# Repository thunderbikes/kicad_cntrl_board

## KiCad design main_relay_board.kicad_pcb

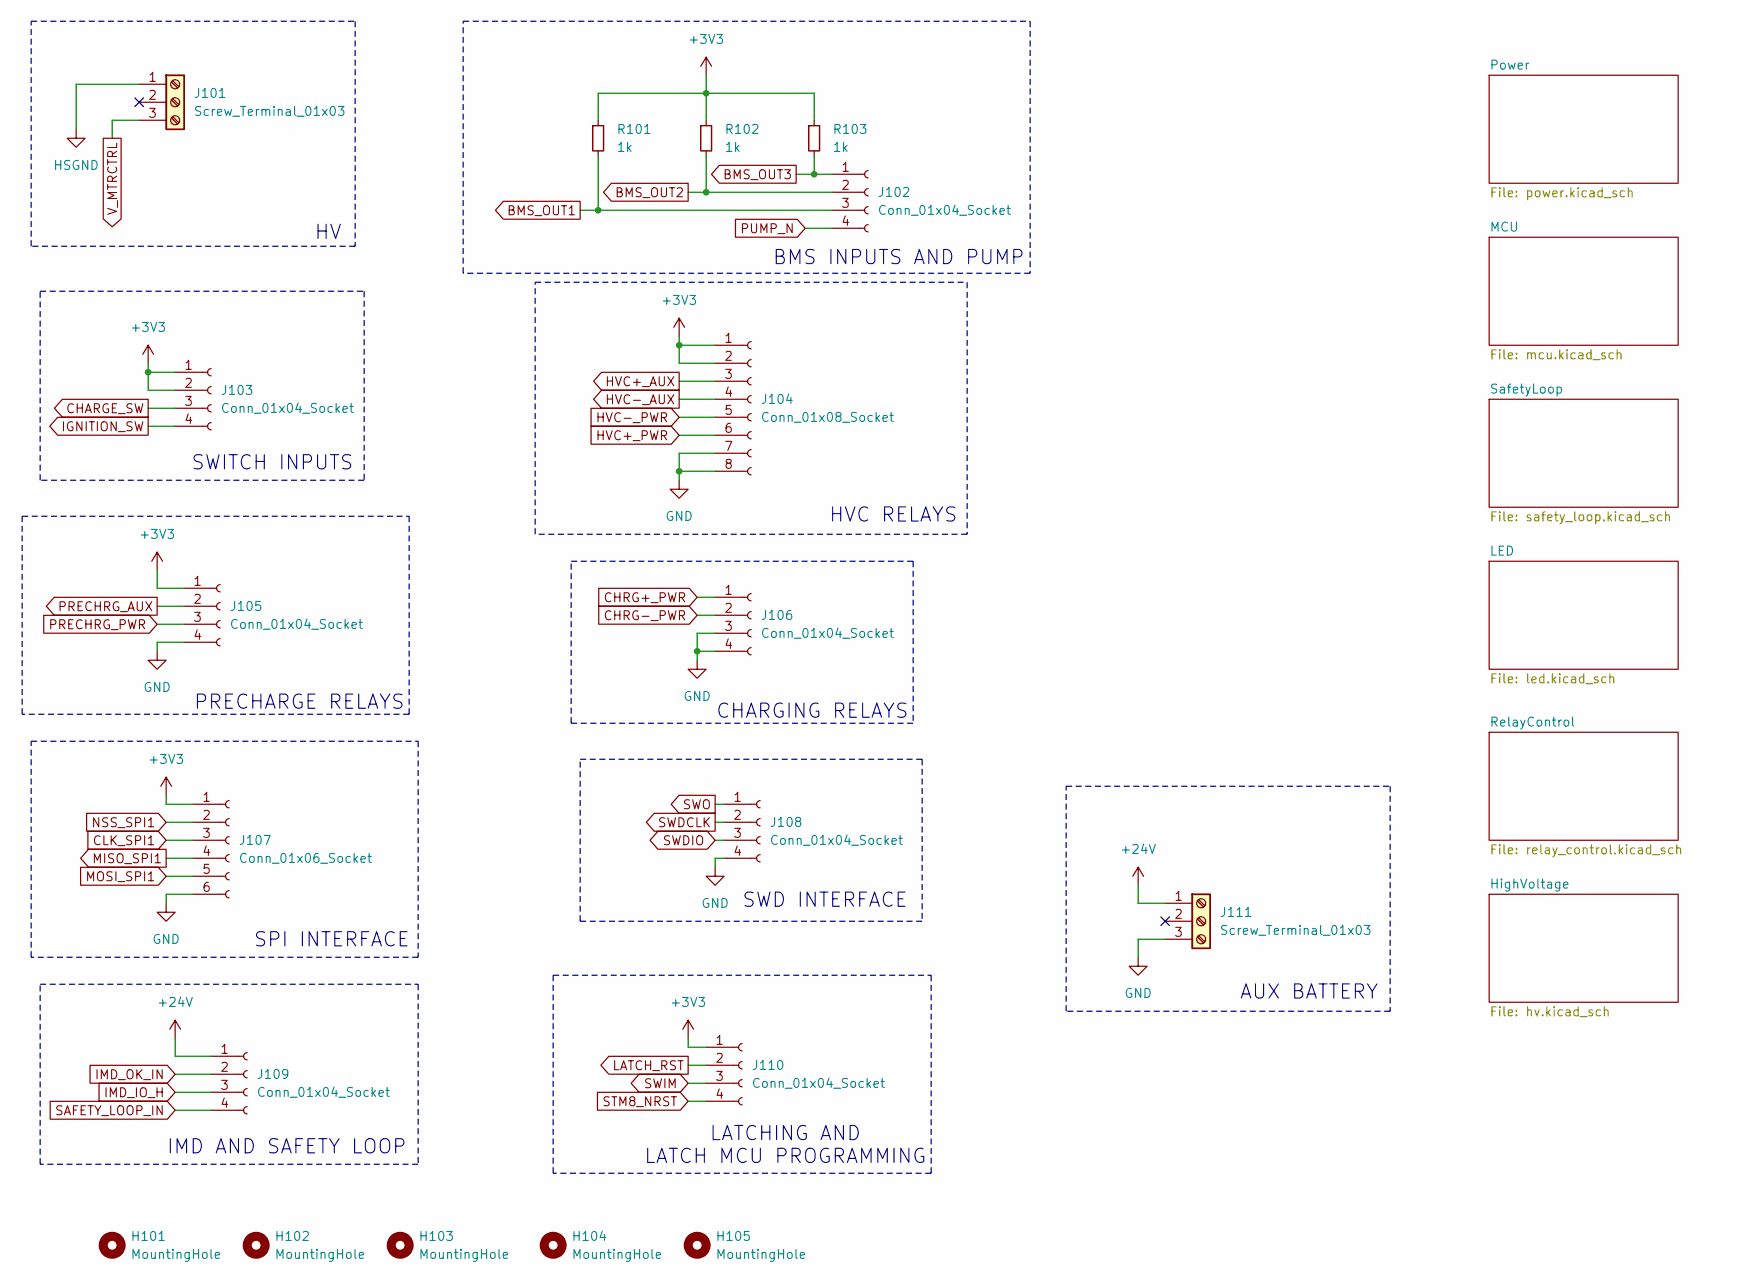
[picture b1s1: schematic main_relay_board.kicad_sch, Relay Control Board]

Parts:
H101, H102, H103, H104, H105: MountingHole; MountingHole_3mm
J101, J111: Screw_Terminal_01x03; TerminalBlock_Phoenix_MKDS-1,5-3-5.08_1x03_P5.08mm_Horizont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
J102, J103, J105, J106, J108, J109, J110: Conn_01x04_Socket; Molex_Mini-Fit_Jr_5566-04A_2x02_P4.20mm_Vertical
J104: Conn_01x08_Socket; Molex_Mini-Fit_Jr_5566-08A_2x04_P4.20mm_Vertical
J107: Conn_01x06_Socket; Molex_Mini-Fit_Jr_5566-06A_2x03_P4.20mm_Vertical
R101, R102, R103: 1k; R_0603_1608Metric; LCSC C22548

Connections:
+24V: J109.1, J111.1; also elsewhere on the board
BMS_OUT1: J102.3, R101.2; also elsewhere on the board
BMS_OUT2: J102.2, R102.2; also elsewhere on the board
BMS_OUT3: J102.1, R103.2; also elsewhere on the board
CHARGE_SW: J103.3; also elsewhere on the board
CHRG+_PWR: J106.1; also elsewhere on the board
CHRG-_PWR: J106.2; also elsewhere on the board
CLK_SPI1: J107.3; also elsewhere on the board
HVC+_AUX: J104.3; also elsewhere on the board
HVC+_PWR: J104.6; also elsewhere on the board
HVC-_AUX: J104.4; also elsewhere on the board
HVC-_PWR: J104.5; also elsewhere on the board
IGNITION_SW: J103.4; also elsewhere on the board
IMD_IO_H: J109.3; also elsewhere on the board
IMD_OK_IN: J109.2; also elsewhere on the board
LATCH_RST: J110.2; also elsewhere on the board
MISO_SPI1: J107.4; also elsewhere on the board
MOSI_SPI1: J107.5; also elsewhere on the board
NSS_SPI1: J107.2; also elsewhere on the board
PRECHRG_AUX: J105.2; also elsewhere on the board
PRECHRG_PWR: J105.3; also elsewhere on the board
PUMP_N: J102.4; also elsewhere on the board
SAFETY_LOOP_IN: J109.4; also elsewhere on the board
STM8_NRST: J110.4; also elsewhere on the board
SWDCLK: J108.2; also elsewhere on the board
SWDIO: J108.3; also elsewhere on the board
SWIM: J110.3; also elsewhere on the board
SWO: J108.1; also elsewhere on the board
V_MTRCTRL: J101.3; also elsewhere on the board

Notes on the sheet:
PRECHARGE RELAYS
BMS INPUTS AND PUMP
AUX BATTERY
CHARGING RELAYS
IMD AND SAFETY LOOP
SWD INTERFACE
SWITCH INPUTS
SPI INTERFACE
LATCHING AND LATCH MCU PROGRAMMING
HVC RELAYS

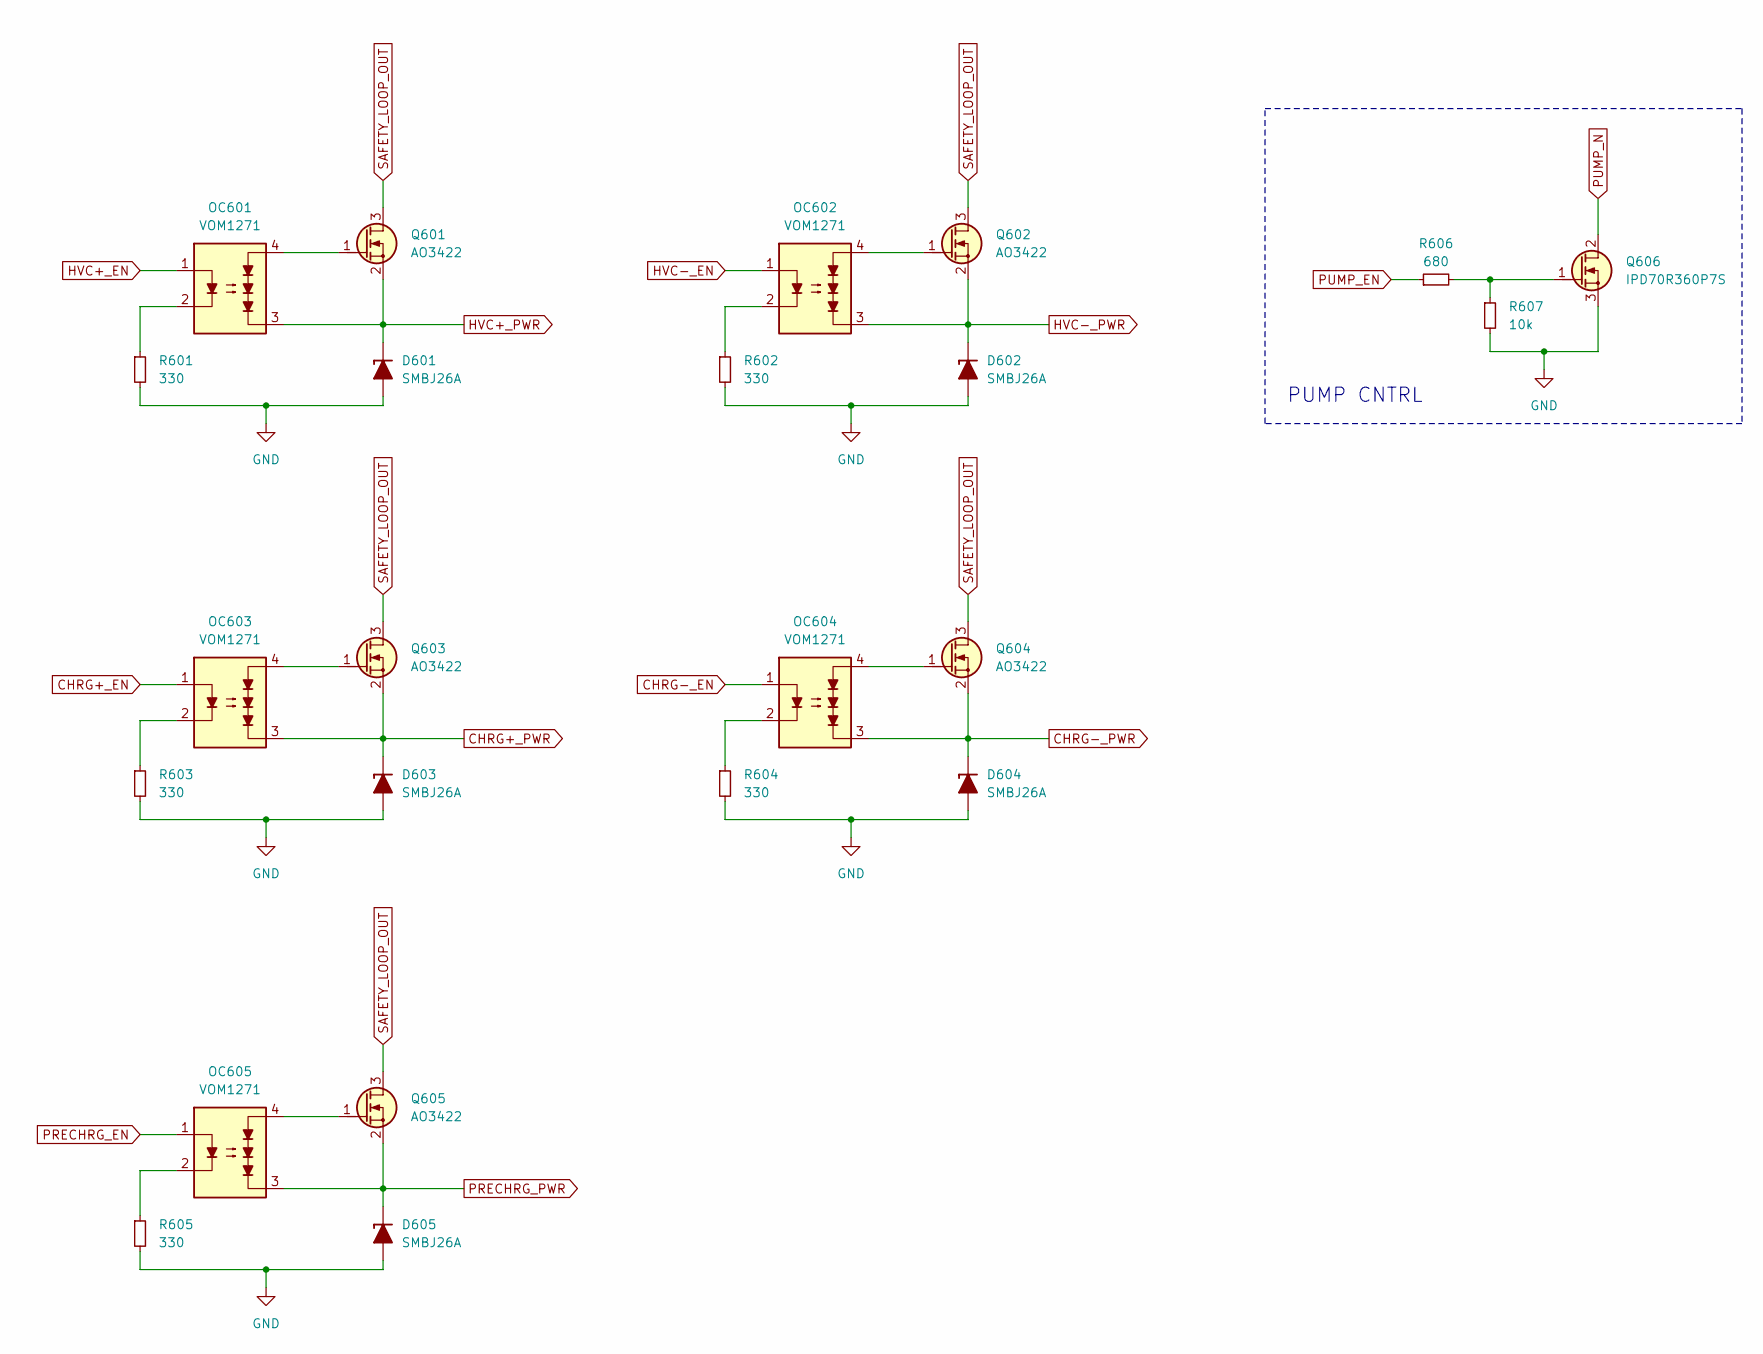
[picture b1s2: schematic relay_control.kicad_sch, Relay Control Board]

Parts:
D601, D602, D603, D604, D605: SMBJ26A; D_SMB; LCSC C2918418
OC601, OC602, OC603, OC604, OC605: VOM1271; SOIC254P695X242-4N; LCSC C146286
Q601, Q602, Q603, Q604, Q605: AO3422; SOT-23; LCSC C37130
Q606: IPD70R360P7S; TO-252-2; LCSC C151509
R601, R602, R603, R604, R605: 330; R_0603_1608Metric; LCSC C25804
R606: 680; R_0603_1608Metric; LCSC C23228
R607: 10k; R_0603_1608Metric; LCSC C25804

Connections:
CHRG+_EN: OC603.1; also elsewhere on the board
CHRG+_PWR: D603.1 (K), OC603.3, Q603.2 (S); also elsewhere on the board
CHRG-_EN: OC604.1; also elsewhere on the board
CHRG-_PWR: D604.1 (K), OC604.3, Q604.2 (S); also elsewhere on the board
HVC+_EN: OC601.1; also elsewhere on the board
HVC+_PWR: D601.1 (K), OC601.3, Q601.2 (S); also elsewhere on the board
HVC-_EN: OC602.1; also elsewhere on the board
HVC-_PWR: D602.1 (K), OC602.3, Q602.2 (S); also elsewhere on the board
unnamed: OC601.2, R601.1
unnamed: OC602.2, R602.1
unnamed: OC603.2, R603.1
unnamed: OC604.2, R604.1
unnamed: OC605.2, R605.1
unnamed: OC601.4, Q601.1 (G)
unnamed: OC602.4, Q602.1 (G)
unnamed: OC603.4, Q603.1 (G)
unnamed: OC604.4, Q604.1 (G)
unnamed: OC605.4, Q605.1 (G)
unnamed: Q606.1 (G), R606.2, R607.1
PRECHRG_EN: OC605.1; also elsewhere on the board
PRECHRG_PWR: D605.1 (K), OC605.3, Q605.2 (S); also elsewhere on the board
PUMP_EN: R606.1; also elsewhere on the board
PUMP_N: Q606.2 (D); also elsewhere on the board
SAFETY_LOOP_OUT: Q601.3 (D), Q602.3 (D), Q603.3 (D), Q604.3 (D), Q605.3 (D); also elsewhere on the board

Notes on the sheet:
PUMP CNTRL

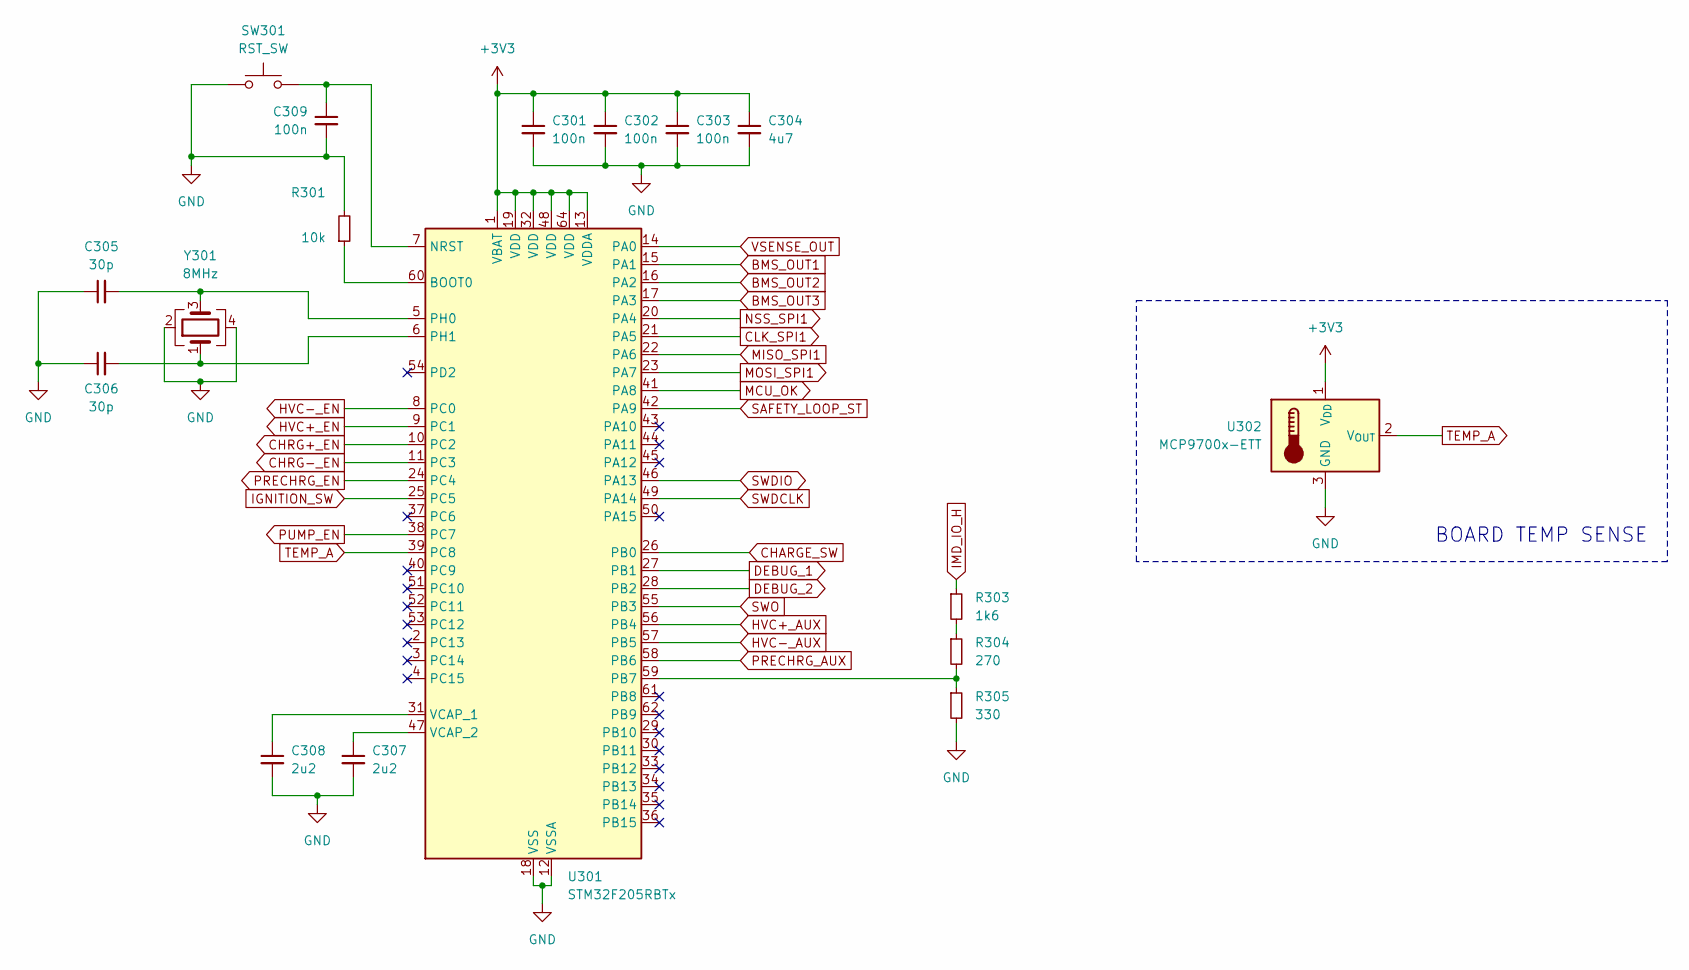
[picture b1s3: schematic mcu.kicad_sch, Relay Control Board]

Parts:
C301, C302, C303, C309: 100n; C_0603_1608Metric; LCSC C1591
C304: 4u7; C_0603_1608Metric; LCSC C108342
C305, C306: 30p; C_0603_1608Metric; LCSC C1853723
C307, C308: 2u2; C_0603_1608Metric; LCSC C99228
R301: 10k; R_0603_1608Metric; LCSC C25804
R303: 1k6; R_0603_1608Metric; LCSC C22847
R304: 270; R_0603_1608Metric; LCSC C22966
R305: 330; R_0603_1608Metric; LCSC C105881
SW301: RST_SW; SW_Tactile_SPST_NO_Straight_CK_PTS636Sx25SMTRLFS; LCSC C318938
U301: STM32F205RBTx; LQFP-64_10x10mm_P0.5mm; LCSC C8364
U302: MCP9700x-ETT; SOT-23; LCSC C127949
Y301: 8MHz; Crystal_SMD_3225-4Pin_3.2x2.5mm; LCSC C2682775

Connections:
BMS_OUT1: U301.15 (PA1); also elsewhere on the board
BMS_OUT2: U301.16 (PA2); also elsewhere on the board
BMS_OUT3: U301.17 (PA3); also elsewhere on the board
CHARGE_SW: U301.26 (PB0); also elsewhere on the board
CHRG+_EN: U301.10 (PC2); also elsewhere on the board
CHRG-_EN: U301.11 (PC3); also elsewhere on the board
CLK_SPI1: U301.21 (PA5); also elsewhere on the board
DEBUG_1: U301.27 (PB1); also elsewhere on the board
DEBUG_2: U301.28 (PB2); also elsewhere on the board
HVC+_AUX: U301.56 (PB4); also elsewhere on the board
HVC+_EN: U301.9 (PC1); also elsewhere on the board
HVC-_AUX: U301.57 (PB5); also elsewhere on the board
HVC-_EN: U301.8 (PC0); also elsewhere on the board
IGNITION_SW: U301.25 (PC5); also elsewhere on the board
IMD_IO_H: R303.1; also elsewhere on the board
MCU_OK: U301.41 (PA8); also elsewhere on the board
MISO_SPI1: U301.22 (PA6); also elsewhere on the board
MOSI_SPI1: U301.23 (PA7); also elsewhere on the board
NSS_SPI1: U301.20 (PA4); also elsewhere on the board
unnamed: R303.2, R304.1
unnamed: R301.1, U301.60 (BOOT0)
unnamed: C309.1, SW301.2, U301.7 (NRST)
unnamed: R304.2, R305.1, U301.59 (PB7)
unnamed: C305.2, U301.5 (PH0), Y301.3
unnamed: C306.2, U301.6 (PH1), Y301.1
unnamed: C308.1, U301.31 (VCAP_1)
unnamed: C307.1, U301.47 (VCAP_2)
PRECHRG_AUX: U301.58 (PB6); also elsewhere on the board
PRECHRG_EN: U301.24 (PC4); also elsewhere on the board
PUMP_EN: U301.38 (PC7); also elsewhere on the board
SAFETY_LOOP_ST: U301.42 (PA9); also elsewhere on the board
SWDCLK: U301.49 (PA14); also elsewhere on the board
SWDIO: U301.46 (PA13); also elsewhere on the board
SWO: U301.55 (PB3); also elsewhere on the board
TEMP_A: U301.39 (PC8), U302.2 (V_{OUT})
VSENSE_OUT: U301.14 (PA0); also elsewhere on the board

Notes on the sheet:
BOARD TEMP SENSE

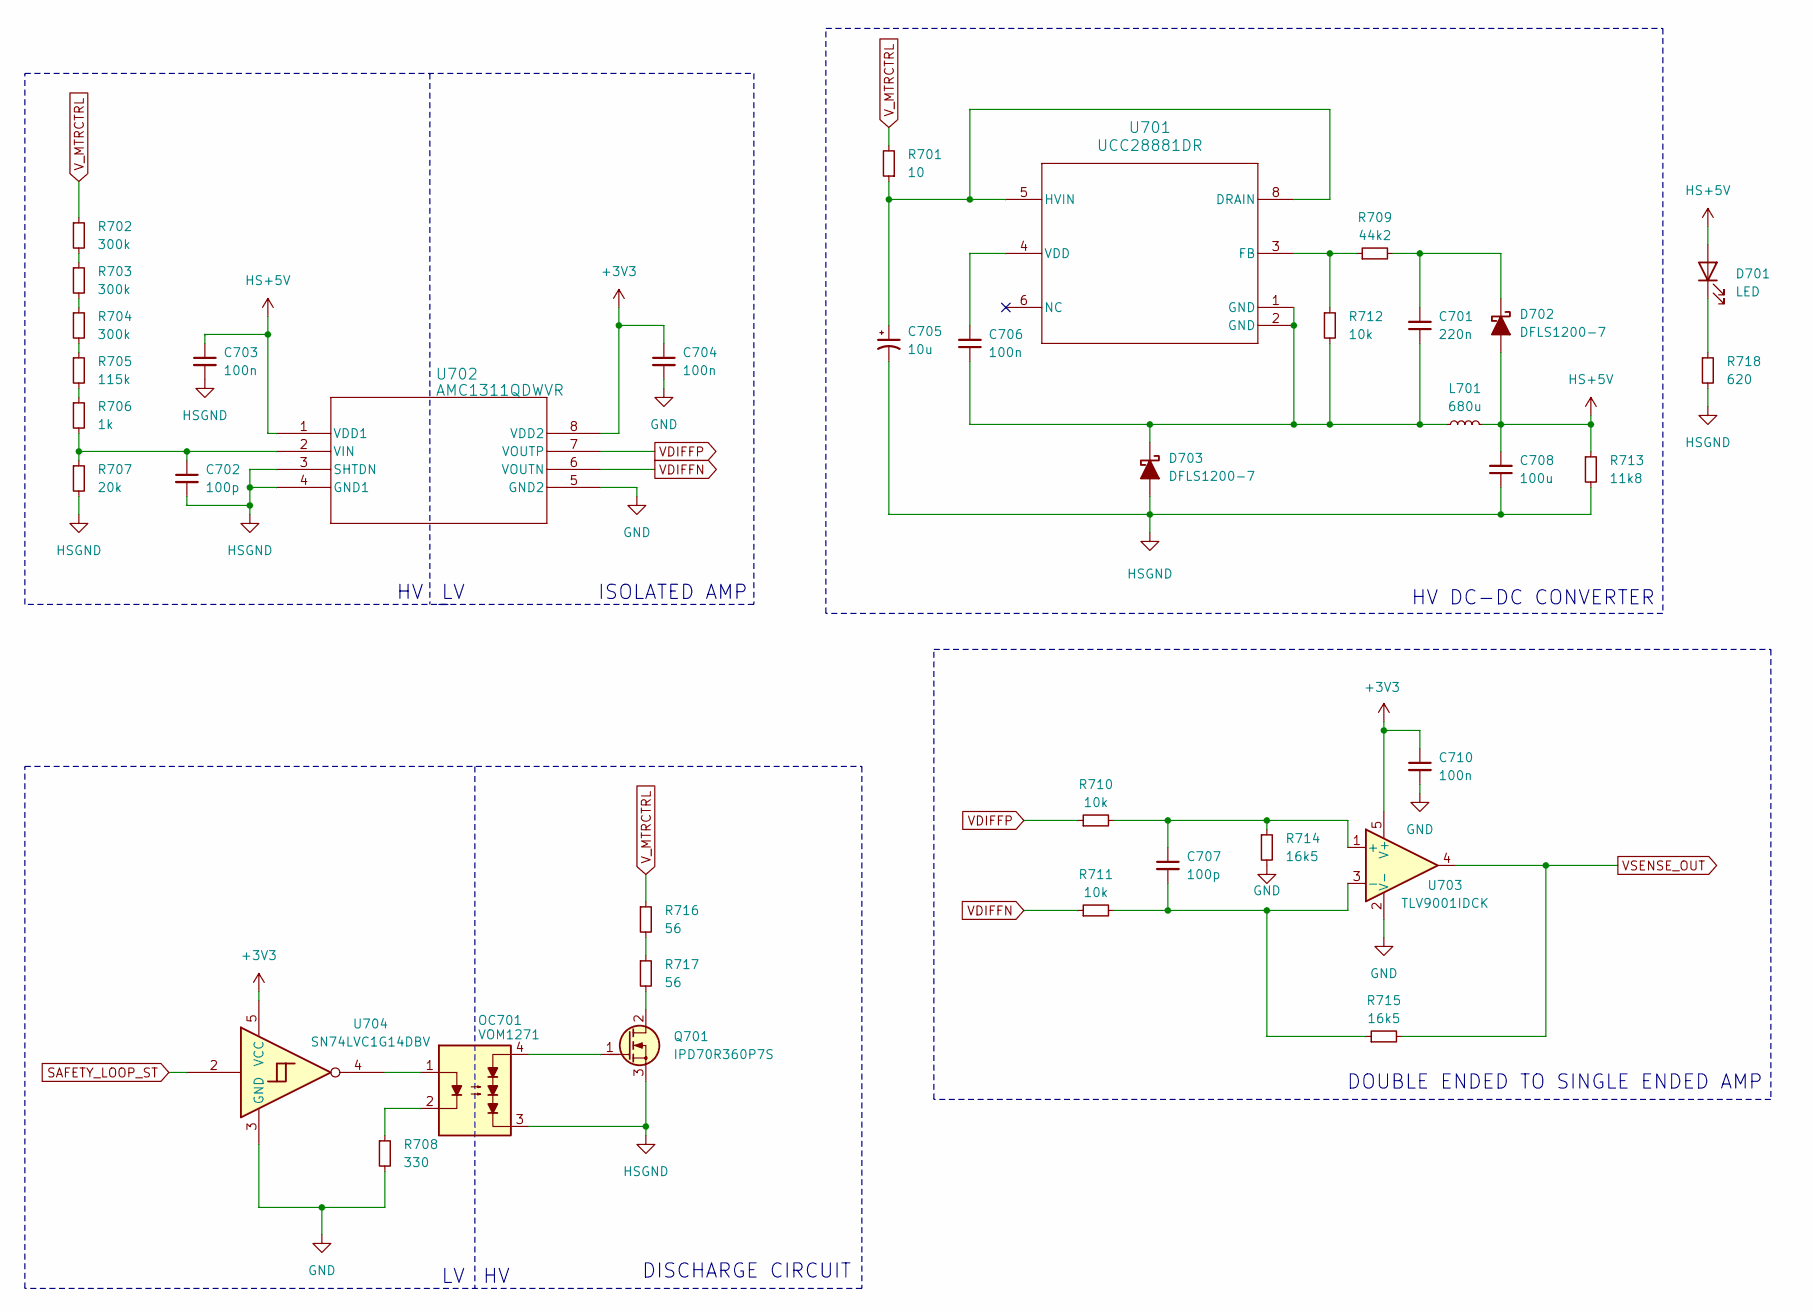
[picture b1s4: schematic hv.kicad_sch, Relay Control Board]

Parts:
C701: 220n; C_0603_1608Metric; LCSC C21120
C702, C707: 100p; C_0603_1608Metric; LCSC C160903
C703, C704, C706, C710: 100n; C_0603_1608Metric; LCSC C1591
C705: 10u; CP_Radial_D10.0mm_P5.00mm; DigiKey P13540-ND
C708: 100u; C_1206_3216Metric; LCSC C15008
D701: LED; LED_0603_1608Metric; LCSC C84263
D702, D703: DFLS1200-7; D_PowerDI-123; LCSC C324985
L701: 680u; L_12x12mm_H8mm; LCSC C2455611
OC701: VOM1271; SOIC254P695X242-4N; LCSC C146286
Q701: IPD70R360P7S; TO-252-2; LCSC C151509
R701: 10; R_0603_1608Metric; LCSC C22859
R702, R703, R704: 300k; R_0603_1608Metric; LCSC C23024
R705: 115k; R_0603_1608Metric; LCSC C3016434
R706: 1k; R_0603_1608Metric; LCSC C22548
R707: 20k; R_0603_1608Metric; LCSC C4184
R708: 330; R_0603_1608Metric; LCSC C105881
R709: 44k2; R_0603_1608Metric; LCSC C23056
R710, R711, R712: 10k; R_0603_1608Metric; LCSC C25804
R713: 11k8; R_0402_1005Metric; LCSC C481934
R714, R715: 16k5; R_0603_1608Metric; LCSC C2933155
R716, R717: 56; TO-247-2_Vertical; DigiKey 273-AP10156RF-ND
R718: 620; R_0603_1608Metric; LCSC C23220
U701: UCC28881DR; D0007A_N; LCSC C544970
U702: AMC1311QDWVR; DWV8_TEX; LCSC C456277
U703: TLV9001IDCK; SOT-353_SC-70-5; LCSC C398362
U704: SN74LVC1G14DBV; SOT-23-5; LCSC C434069

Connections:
HS+5V: C703.1, C708.2, D701.2 (A), D702.2 (A), L701.2, R713.1, U701.6 (+Vout), U702.1 (VDD1)
unnamed: D701.1 (K), R718.1
unnamed: OC701.1, U704.4
unnamed: OC701.2, R708.1
unnamed: Q701.2 (D), R717.2
unnamed: OC701.4, Q701.1 (G)
unnamed: R702.2, R703.1
unnamed: R703.2, R704.1
unnamed: R704.2, R705.1
unnamed: R705.2, R706.1
unnamed: R709.1, R712.1, U701.3 (FB)
unnamed: R716.2, R717.1
SAFETY_LOOP_ST: U704.2; also elsewhere on the board
VDIFFN: R711.1, U702.6 (VOUTN)
VDIFFP: R710.1, U702.7 (VOUTP)
VSENSE_OUT: R715.2, U703.4; also elsewhere on the board
V_MTRCTRL: R701.2, R702.1, R716.1; also elsewhere on the board

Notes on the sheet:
DISCHARGE CIRCUIT
ISOLATED AMP
DOUBLE ENDED TO SINGLE ENDED AMP
HV DC-DC CONVERTER

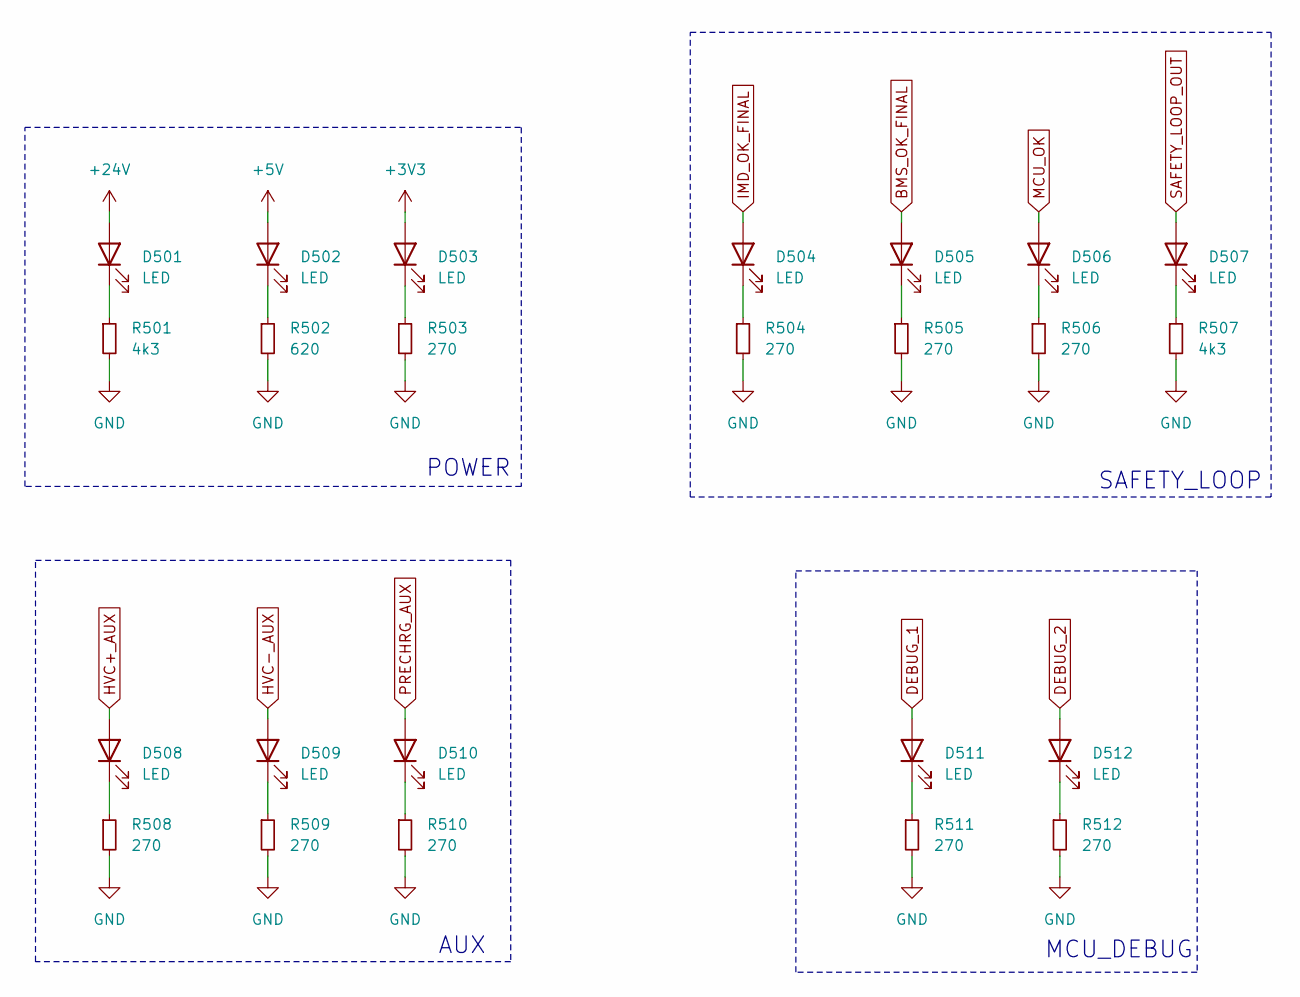
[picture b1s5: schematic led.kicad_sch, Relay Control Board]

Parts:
D501, D502, D503, D504, D505, D506, D507, D508, D509, D510, D511, D512: LED; LED_0603_1608Metric; LCSC C84263
R501, R507: 4k3; R_0603_1608Metric; LCSC C23159
R502: 620; R_0603_1608Metric; LCSC C23220
R503, R504, R505, R506, R508, R509, R510, R511, R512: 270; R_0603_1608Metric; LCSC C22966

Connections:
+24V: D501.2 (A); also elsewhere on the board
BMS_OK_FINAL: D505.2 (A); also elsewhere on the board
DEBUG_1: D511.2 (A); also elsewhere on the board
DEBUG_2: D512.2 (A); also elsewhere on the board
HVC+_AUX: D508.2 (A); also elsewhere on the board
HVC-_AUX: D509.2 (A); also elsewhere on the board
IMD_OK_FINAL: D504.2 (A); also elsewhere on the board
MCU_OK: D506.2 (A); also elsewhere on the board
unnamed: D501.1 (K), R501.1
unnamed: D502.1 (K), R502.1
unnamed: D503.1 (K), R503.1
unnamed: D504.1 (K), R504.1
unnamed: D505.1 (K), R505.1
unnamed: D506.1 (K), R506.1
unnamed: D507.1 (K), R507.1
unnamed: D508.1 (K), R508.1
unnamed: D509.1 (K), R509.1
unnamed: D510.1 (K), R510.1
unnamed: D511.1 (K), R511.1
unnamed: D512.1 (K), R512.1
PRECHRG_AUX: D510.2 (A); also elsewhere on the board
SAFETY_LOOP_OUT: D507.2 (A); also elsewhere on the board

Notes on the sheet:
SAFETY_LOOP
MCU_DEBUG
POWER
AUX

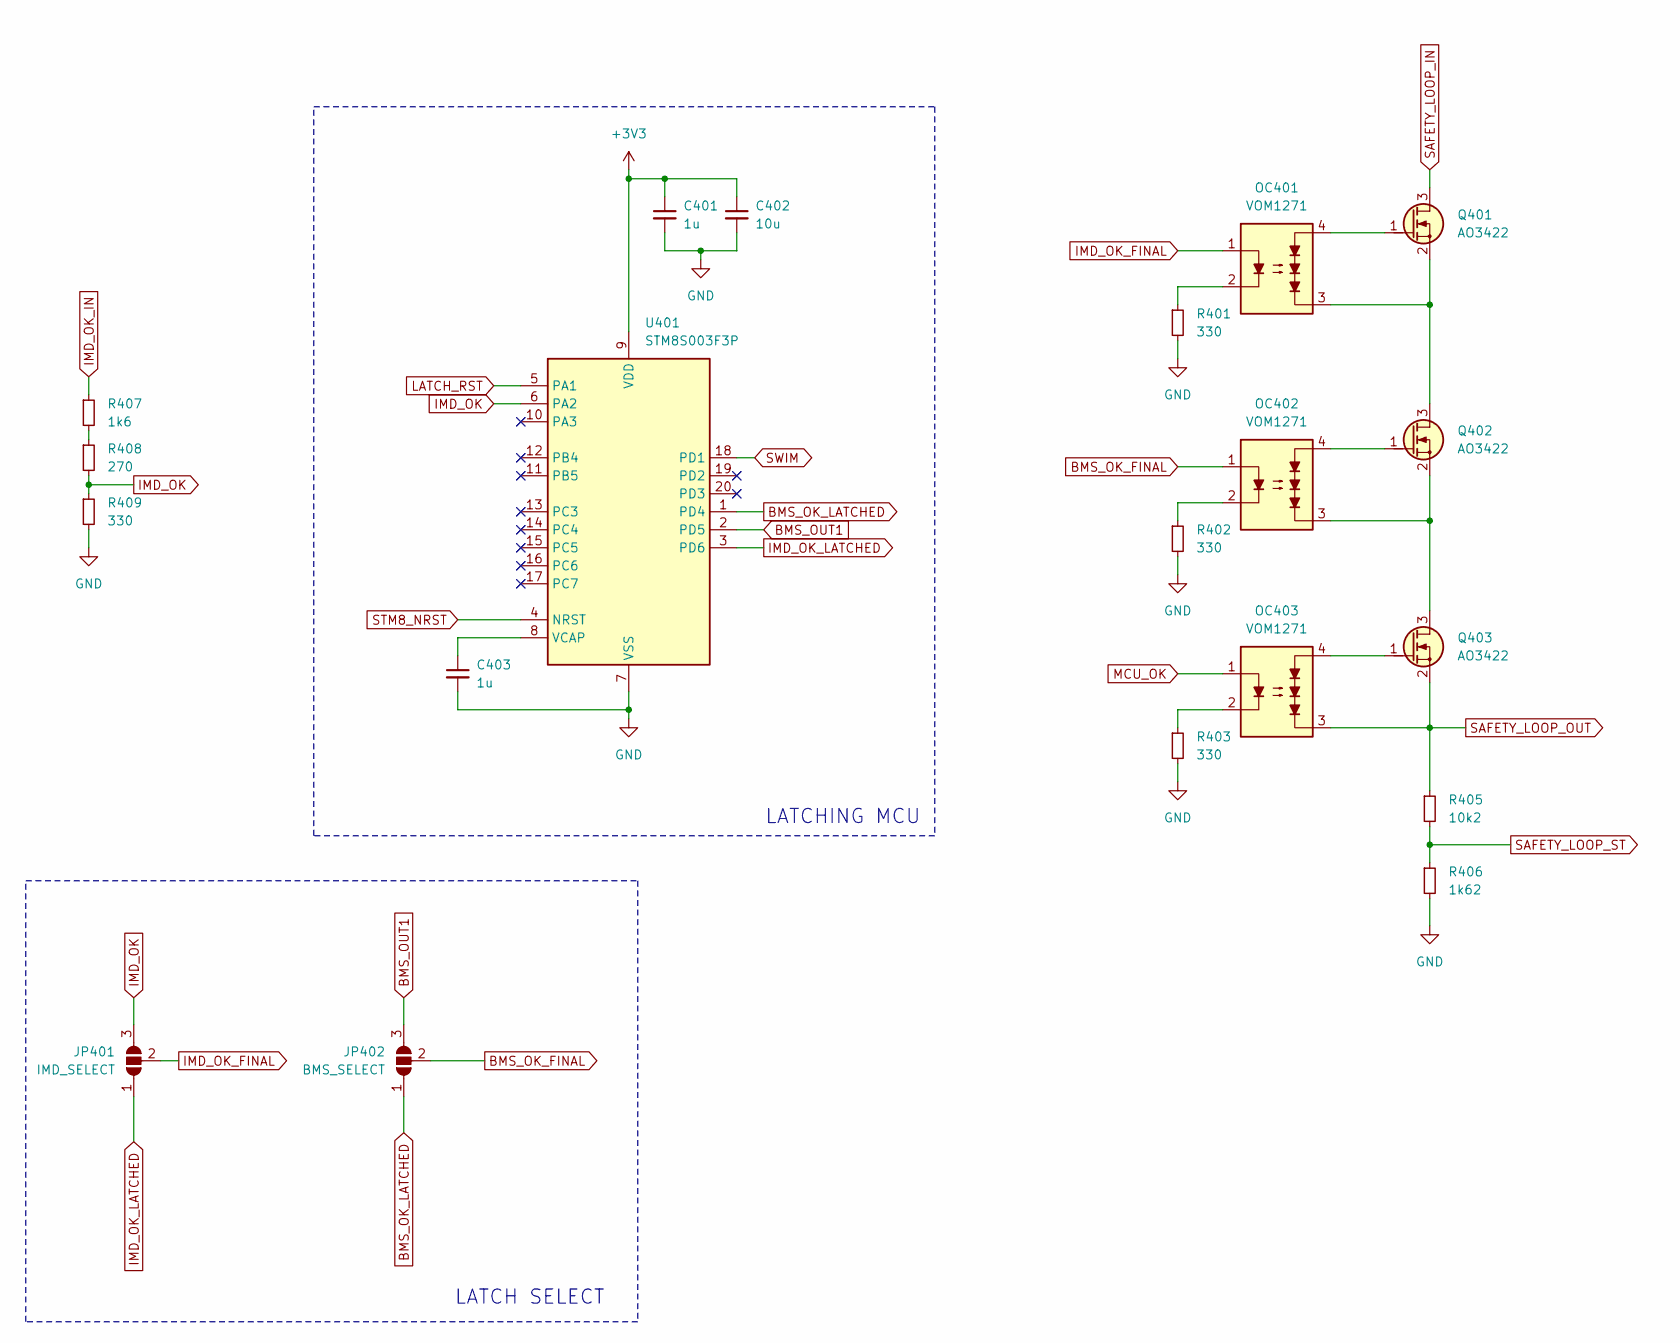
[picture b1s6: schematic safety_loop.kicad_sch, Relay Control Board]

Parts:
C401, C403: 1u; C_0603_1608Metric; LCSC C59302
C402: 10u; C_0603_1608Metric; LCSC C91606
JP401: IMD_SELECT; SolderJumper-3_P1.3mm_Open_Pad1.0x1.5mm
JP402: BMS_SELECT; SolderJumper-3_P1.3mm_Open_Pad1.0x1.5mm
OC401, OC402, OC403: VOM1271; SOIC254P695X242-4N; LCSC C146286
Q401, Q402, Q403: AO3422; SOT-23; LCSC C37130
R401, R402, R403, R409: 330; R_0603_1608Metric; LCSC C105881
R405: 10k2; R_0603_1608Metric; LCSC C22772
R406: 1k62; R_0603_1608Metric; LCSC C22844
R407: 1k6; R_0603_1608Metric; LCSC C22847
R408: 270; R_0603_1608Metric; LCSC C22966
U401: STM8S003F3P; TSSOP-20_4.4x6.5mm_P0.65mm; LCSC C52717

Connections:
BMS_OK_FINAL: JP402.2 (C), OC402.1; also elsewhere on the board
BMS_OK_LATCHED: JP402.1 (A), U401.1 (PD4)
BMS_OUT1: JP402.3 (B), U401.2 (PD5); also elsewhere on the board
IMD_OK: JP401.3 (B), R408.2, R409.1, U401.6 (PA2)
IMD_OK_FINAL: JP401.2 (C), OC401.1; also elsewhere on the board
IMD_OK_IN: R407.1; also elsewhere on the board
IMD_OK_LATCHED: JP401.1 (A), U401.3 (PD6)
LATCH_RST: U401.5 (PA1); also elsewhere on the board
MCU_OK: OC403.1; also elsewhere on the board
unnamed: OC401.2, R401.1
unnamed: OC402.2, R402.1
unnamed: OC403.2, R403.1
unnamed: OC401.4, Q401.1 (G)
unnamed: OC401.3, Q401.2 (S), Q402.3 (D)
unnamed: OC402.4, Q402.1 (G)
unnamed: OC402.3, Q402.2 (S), Q403.3 (D)
unnamed: OC403.4, Q403.1 (G)
unnamed: R407.2, R408.1
unnamed: C403.1, U401.8 (VCAP)
SAFETY_LOOP_IN: Q401.3 (D); also elsewhere on the board
SAFETY_LOOP_OUT: OC403.3, Q403.2 (S), R405.1; also elsewhere on the board
SAFETY_LOOP_ST: R405.2, R406.1; also elsewhere on the board
STM8_NRST: U401.4 (NRST); also elsewhere on the board
SWIM: U401.18 (PD1); also elsewhere on the board

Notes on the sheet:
LATCHING MCU
LATCH SELECT

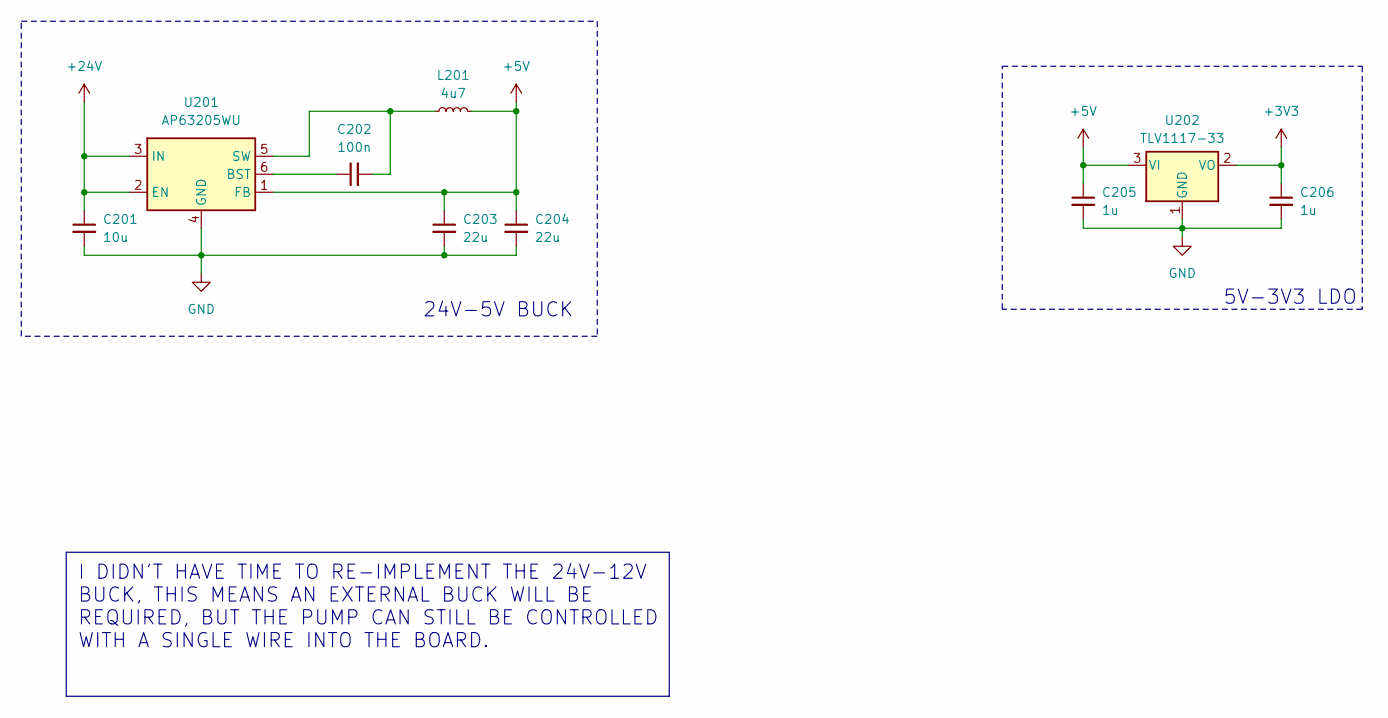
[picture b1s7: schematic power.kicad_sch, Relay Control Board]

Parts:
C201: 10u; C_0603_1608Metric; LCSC C91606
C202: 100n; C_0603_1608Metric; LCSC C1591
C203, C204: 22u; C_0603_1608Metric; LCSC C86295
C205, C206: 1u; C_0603_1608Metric; LCSC C59302
L201: 4u7; L_1210_3225Metric; LCSC C5331021
U201: AP63205WU; TSOT-23-6; LCSC C2071056
U202: TLV1117-33; SOT-223-3_TabPin2; LCSC C37359

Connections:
+24V: C201.1, U201.2 (EN), U201.3 (IN); also elsewhere on the board
unnamed: C202.1, U201.6 (BST)
unnamed: C202.2, L201.1, U201.5 (SW)

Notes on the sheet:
I DIDN'T HAVE TIME TO RE-IMPLEMENT THE 24V-12V BUCK, THIS MEANS AN EXTERNAL BUCK WILL BE REQUIRED, BUT THE PUMP CAN STILL BE CONTROLLED WITH A SINGLE WIRE INTO THE BOARD.
5V-3V3 LDO
24V-5V BUCK

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
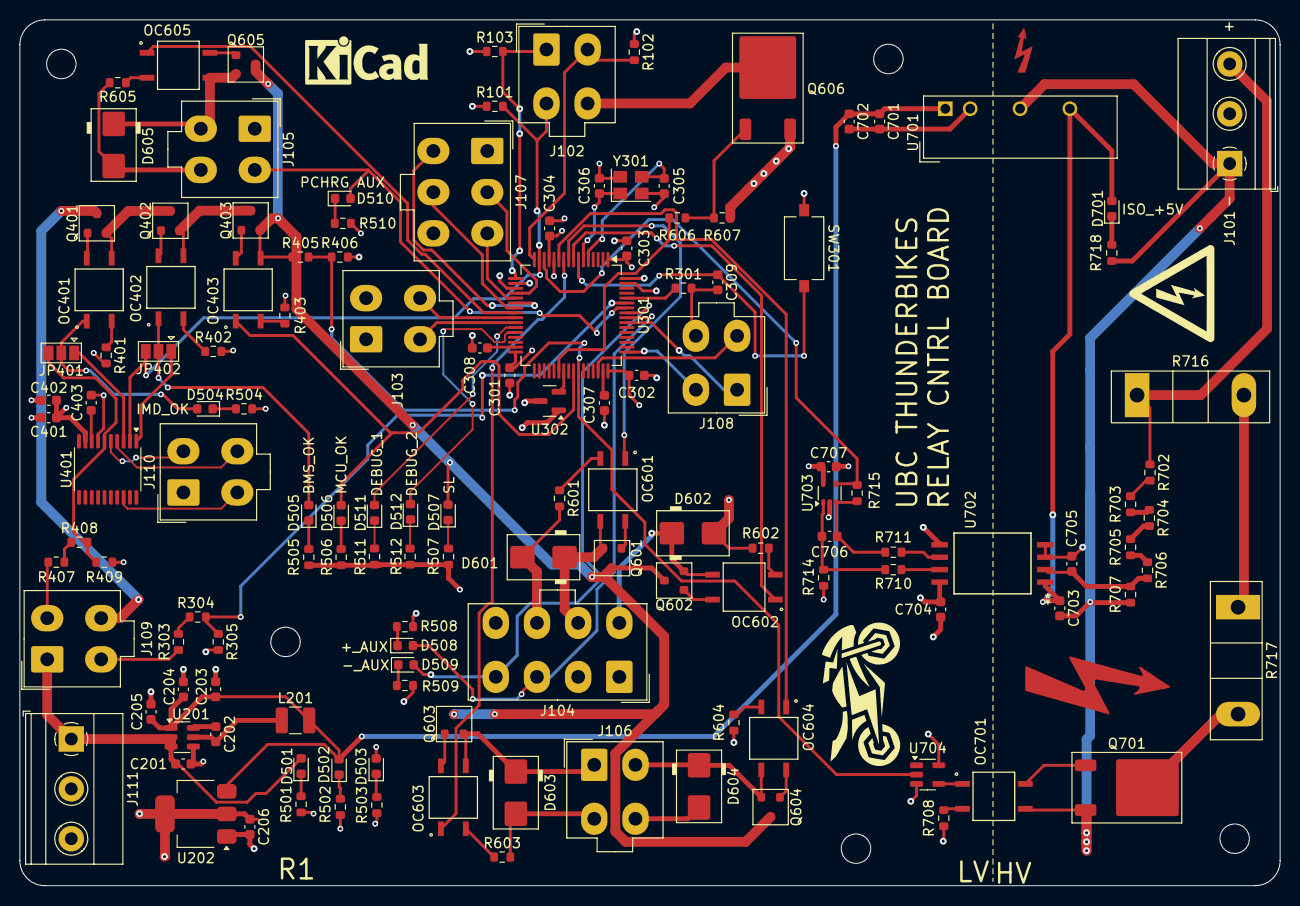
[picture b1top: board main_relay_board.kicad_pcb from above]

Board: 4 copper layers, 128.5 x 88.3 mm, 140 parts (0 on the bottom side), 110 nets.

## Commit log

2024-07-09 existing board with old HV buck
2024-07-09 started working on it
2024-07-10 finished...
2024-07-11 switched to an isolated dcdc transformer from LS 5V
